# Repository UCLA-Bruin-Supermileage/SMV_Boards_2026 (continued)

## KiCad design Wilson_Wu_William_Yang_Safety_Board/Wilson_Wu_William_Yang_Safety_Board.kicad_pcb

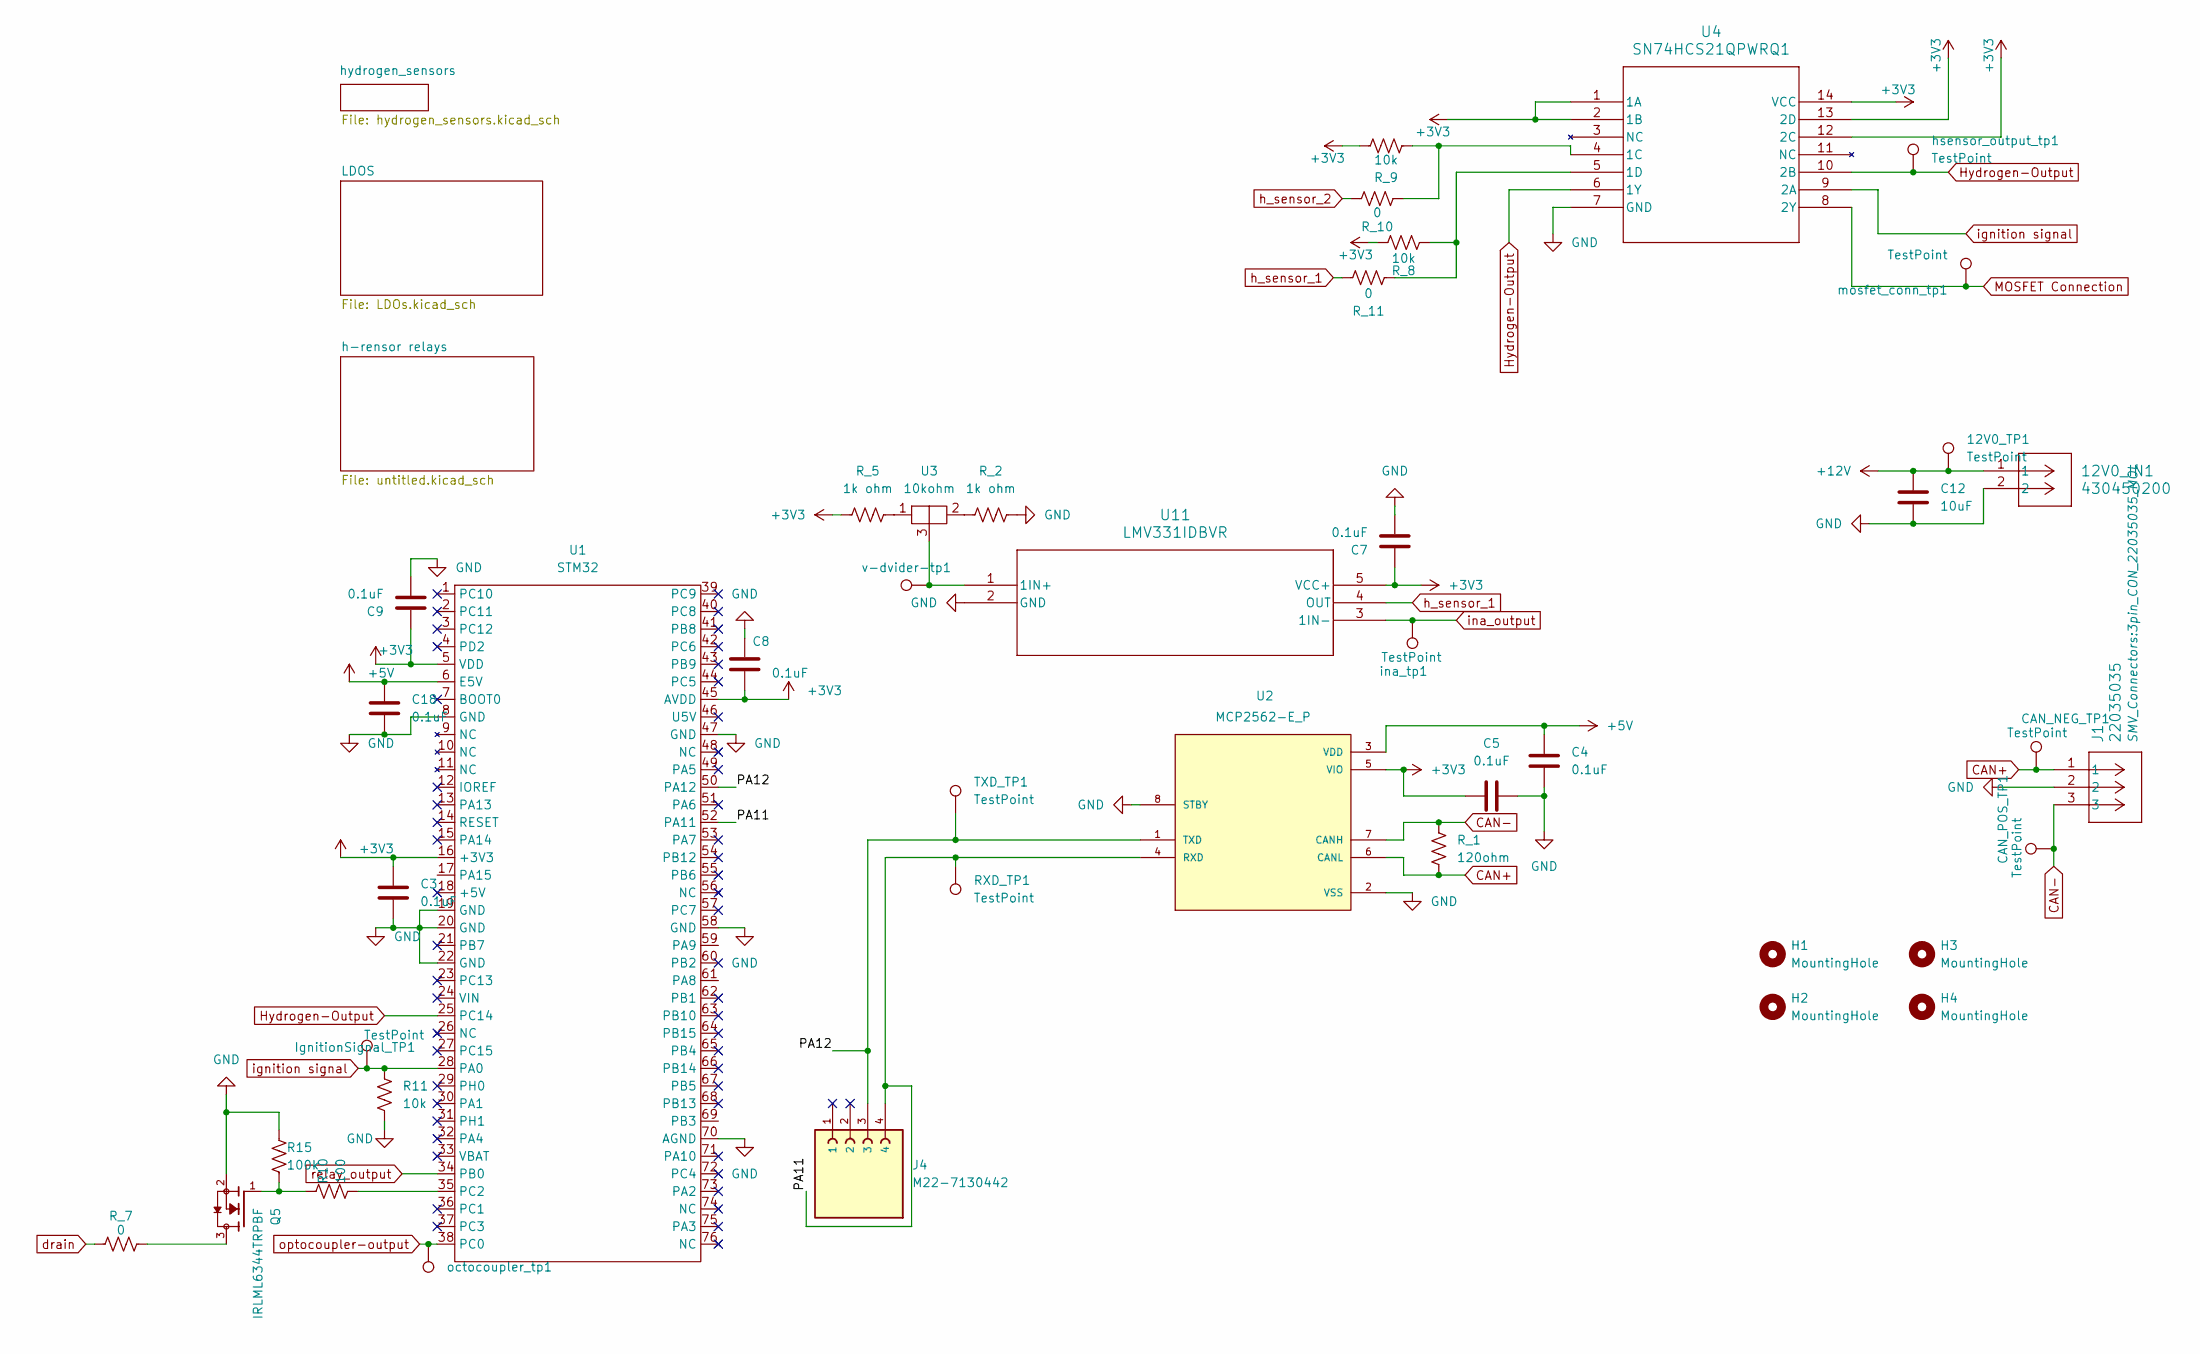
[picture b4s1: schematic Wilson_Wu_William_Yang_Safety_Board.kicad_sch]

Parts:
12V0_IN1: 430450200; CONN_SD-43045-001_02_MOL
12V0_TP1: TestPoint; TestPoint_Pad_D1.0mm
C3, C4, C5, C7, C8, C9, C18: 0.1uF; C_0805_2012Metric
C12: 10uF; C_0805_2012Metric
CAN_NEG_TP1: TestPoint; TestPoint_Pad_D1.0mm
CAN_POS_TP1: TestPoint; TestPoint_Pad_D1.0mm
H1, H2, H3, H4: MountingHole; MountingHole_3.2mm_M3
IgnitionSignal_TP1: TestPoint; TestPoint_Pad_D1.0mm
J1: 22035035; 3pin_CON_22035035_MOL
J4: M22-7130442; HARWIN_M22-7130442
Q5: IRLML6344TRPBF; TRANS_IRLML6344TRPBF; PARTREV December 19, 2014
R10: 100; R_0805_2012Metric
R11: 10k; R_0805_2012Metric
R15: 100k; R_0805_2012Metric
RXD_TP1: TestPoint; TestPoint_Pad_D1.0mm
R_1: 120ohm; R_0805_2012Metric
R_2, R_5: 1k ohm; R_0805_2012Metric
R_7, R_10, R_11: 0; R_0805_2012Metric
R_8, R_9: 10k; R_0805_2012Metric
TXD_TP1: TestPoint; TestPoint_Pad_D1.0mm
U1: STM32; MODULE_NUCLEO-F446RE
U2: MCP2562-E_P; SOIC127P600X175-8N; PARTREV C
U3: 10kohm; Potentiometer_Vishay_T73XW_Horizontal
U4: SN74HCS21QPWRQ1; TSSOP14_PW_TEX-M
U11: LMV331IDBVR; DBV5
hsensor_output_tp1: TestPoint; TestPoint_Pad_D1.0mm
ina_tp1: TestPoint; TestPoint_Pad_D1.0mm
mosfet_conn_tp1: TestPoint; TestPoint_Pad_D1.0mm
octocoupler_tp1: V_DIVIDED; TestPoint_Pad_D1.0mm
v-dvider-tp1: v-dvider-tp; TestPoint_Pad_D1.0mm

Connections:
+3V3: C3.1, C5.2, C7.2, C8.2, C9.2, R_5.1, R_8.2, R_9.2, U1.5 (VDD), U1.16 (+3V3), U1.45 (AVDD), U2.5 (VIO), U4.1 (1A), U4.2 (1B), U4.12 (2C), U4.13 (2D), U4.14 (VCC), U11.5 (VCC+); also elsewhere on the board
+5V: C4.2, C18.2, U1.6 (E5V), U2.3 (VDD); also elsewhere on the board
+12V: 12V0_IN1.1, 12V0_TP1.1, C12.2; also elsewhere on the board
/PA11: J4.4, RXD_TP1.1, U1.52 (PA11), U2.4 (RXD)
/PA12: J4.3, TXD_TP1.1, U1.50 (PA12), U2.1 (TXD)
CAN+: CAN_NEG_TP1.1, J1.1, R_1.2, U2.6 (CANL)
CAN-: CAN_POS_TP1.1, J1.3, R_1.1, U2.7 (CANH)
GND: 12V0_IN1.2, C3.2, C4.1, C5.1, C7.1, C8.1, C9.1, C12.1, C18.1, J1.2, Q5.2, R11.1, R15.2, R_2.2, U1.8 (GND), U1.19 (GND), U1.20 (GND), U1.22 (GND), U1.47 (GND), U1.58 (GND), U1.70 (AGND), U2.2 (VSS), U2.8 (STBY), U4.7 (GND), U11.2 (GND); also elsewhere on the board
Hydrogen-Output: U1.25 (PC14), U4.6 (1Y), U4.10 (2B), hsensor_output_tp1.1
MOSFET Connection: U4.8 (2Y), mosfet_conn_tp1.1; also elsewhere on the board
unnamed: Q5.1, R10.2, R15.1
unnamed: Q5.3, R_7.2
unnamed: R_2.1, U3.2
unnamed: R_5.2, U3.1
unnamed: R10.1, U1.35 (PC2)
unnamed: R_9.1, R_10.1, U4.4 (1C)
unnamed: R_8.1, R_11.1, U4.5 (1D)
unnamed: U3.3, U11.1 (1IN+), v-dvider-tp1.1
drain: R_7.1; also elsewhere on the board
h_sensor_1: R_11.2, U11.4 (OUT)
h_sensor_2: R_10.2; also elsewhere on the board
ignition signal: IgnitionSignal_TP1.1, R11.2, U1.28 (PA0), U4.9 (2A)
ina_output: U11.3 (1IN-), ina_tp1.1; also elsewhere on the board
optocoupler-output: U1.38 (PC0), octocoupler_tp1.1; also elsewhere on the board
relay_output: U1.34 (PB0); also elsewhere on the board

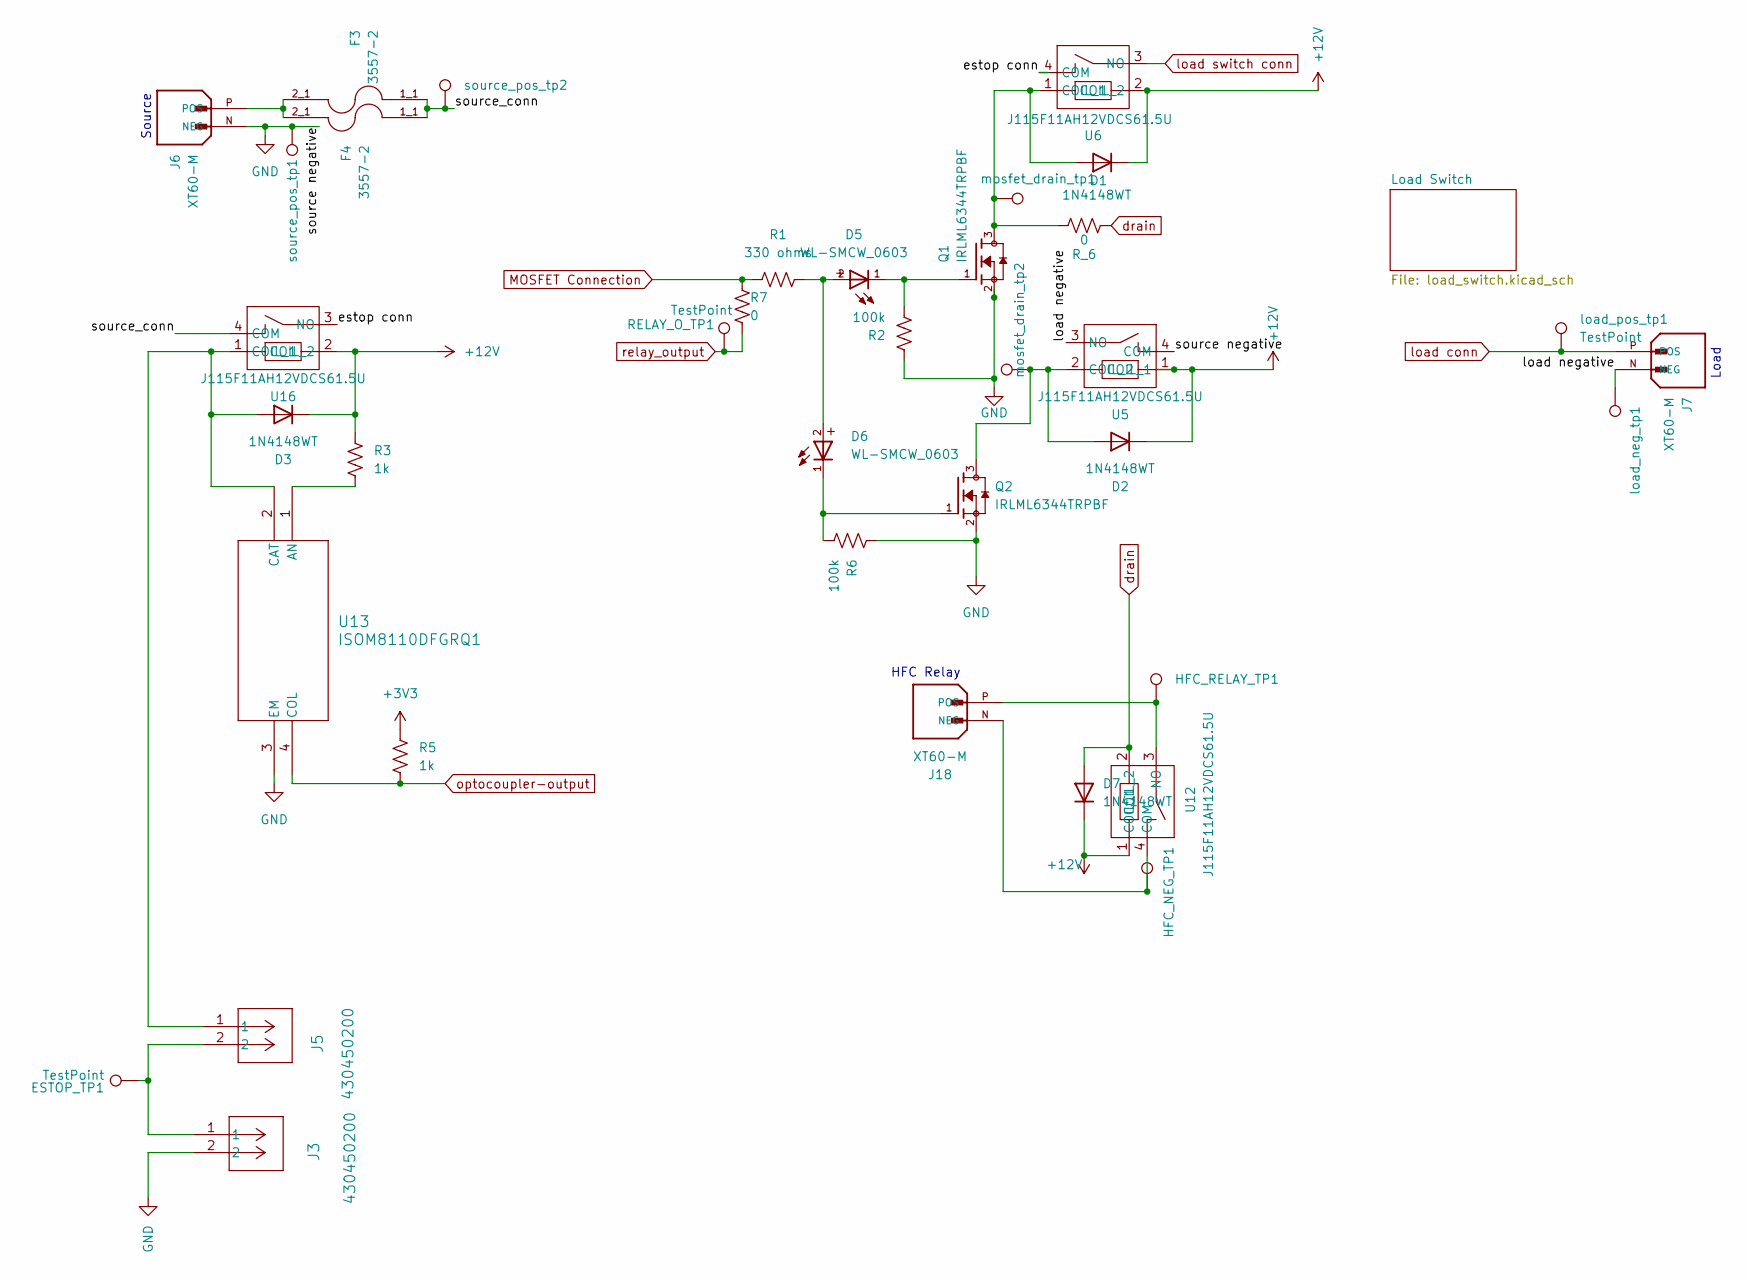
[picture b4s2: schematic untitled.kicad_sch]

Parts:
D1, D2, D3, D7: 1N4148WT; D_SOD-523
D5, D6: WL-SMCW_0603; WL-SMCW_0603(diode)
ESTOP_TP1: TestPoint; TestPoint_Pad_D1.0mm
F3, F4: 3557-2; FUSE_3557-2; PARTREV A
HFC_NEG_TP1: V_DIVIDED; TestPoint_Pad_D1.0mm
HFC_RELAY_TP1: V_DIVIDED; TestPoint_Pad_D1.0mm
J3, J5: 430450200; CONN_SD-43045-001_02_MOL
J6, J7, J18: XT60-M; AMASS_XT60-M; PARTREV V1.2
Q1, Q2: IRLML6344TRPBF; TRANS_IRLML6344TRPBF; PARTREV December 19, 2014
R1: 330 ohms; R_0805_2012Metric
R2, R6: 100k; R_0805_2012Metric
R3, R5: 1k; 0603_resistors
R7: 0; R_0805_2012Metric
RELAY_O_TP1: TestPoint; TestPoint_Pad_D1.0mm
R_6: 0; R_0805_2012Metric
U5, U6, U12, U16: J115F11AH12VDCS61.5U; J115F11AH12VDCS615U
U13: ISOM8110DFGRQ1; DFG0004A_TEX
load_neg_tp1: V_DIVIDED; TestPoint_Pad_D1.0mm
load_pos_tp1: TestPoint; TestPoint_Pad_D1.0mm
mosfet_drain_tp1, mosfet_drain_tp2: V_DIVIDED; TestPoint_Pad_D1.0mm
source_pos_tp1, source_pos_tp2: V_DIVIDED; TestPoint_Pad_D1.0mm

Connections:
+3V3: R5.1; also elsewhere on the board
+12V: D1.1 (K), D2.1 (K), D3.1 (K), D7.1 (K), R3.1, U5.1 (COIL_1), U6.2 (COIL_2), U12.1 (COIL_1), U16.2 (COIL_2); also elsewhere on the board
/h-rensor relays/estop conn: U6.4 (COM), U16.3 (NO)
/h-rensor relays/load negative: J7.N (NEG), U5.3 (NO), load_neg_tp1.1
/h-rensor relays/source_conn: F3.1_1, F4.1_1, U16.4 (COM), source_pos_tp2.1
GND: J3.2, J6.N (NEG), Q1.2, Q2.2, R2.2, R6.2, U5.4 (COM), U13.3 (EM), source_pos_tp1.1; also elsewhere on the board
MOSFET Connection: R1.2, R7.2; also elsewhere on the board
unnamed: D1.2 (A), Q1.3, R_6.2, U6.1 (COIL_1), mosfet_drain_tp1.1
unnamed: D2.2 (A), Q2.3, U5.2 (COIL_2), mosfet_drain_tp2.1
unnamed: D3.2 (A), J5.1, U13.2 (CAT), U16.1 (COIL_1)
unnamed: D5.1, Q1.1, R2.1
unnamed: D5.2, D6.2, R1.1
unnamed: D6.1, Q2.1, R6.1
unnamed: ESTOP_TP1.1, J3.1, J5.2
unnamed: F3.2_1, F4.2_1, J6.P (POS)
unnamed: HFC_NEG_TP1.1, J18.N (NEG), U12.4 (COM)
unnamed: HFC_RELAY_TP1.1, J18.P (POS), U12.3 (NO)
unnamed: R3.2, U13.1 (AN)
drain: D7.2 (A), R_6.1, U12.2 (COIL_2); also elsewhere on the board
load conn: J7.P (POS), load_pos_tp1.1; also elsewhere on the board
load switch conn: U6.3 (NO); also elsewhere on the board
optocoupler-output: R5.2, U13.4 (COL); also elsewhere on the board
relay_output: R7.1, RELAY_O_TP1.1; also elsewhere on the board

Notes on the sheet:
Load
Source
HFC Relay

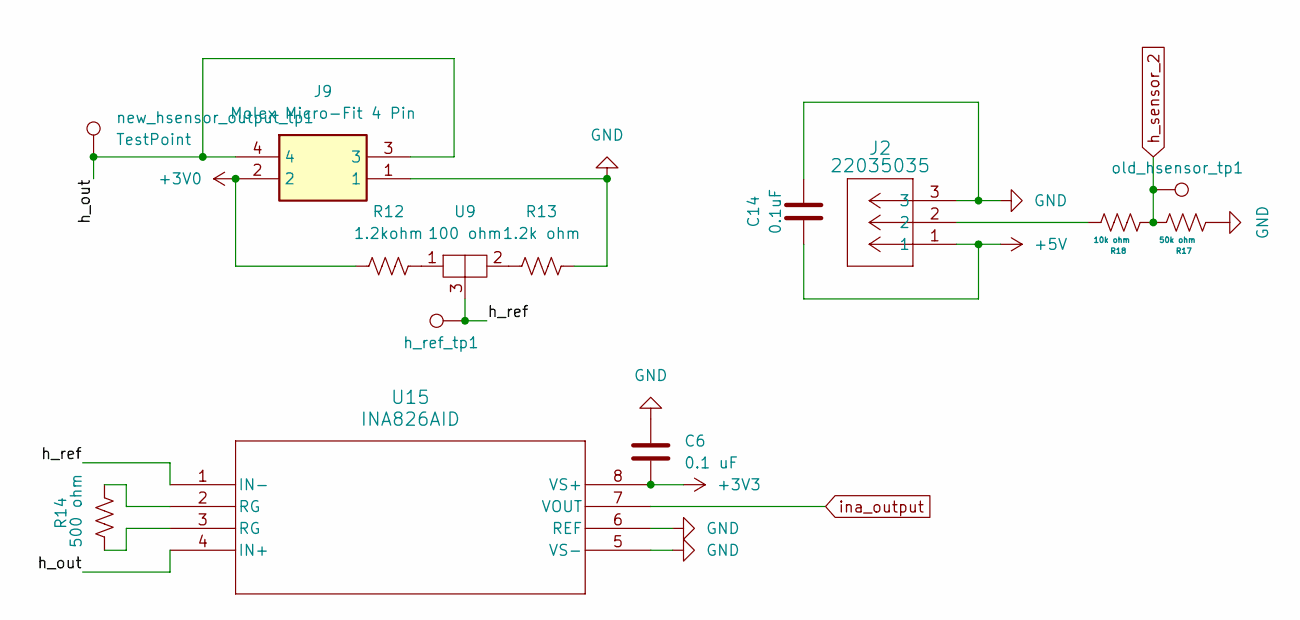
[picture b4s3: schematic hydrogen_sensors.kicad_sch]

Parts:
C6: 0.1 uF; C_0805_2012Metric
C14: 0.1uF; C_0805_2012Metric
J2: 22035035; 3pin_CON_22035035_MOL
J9: Molex Micro-Fit 4 Pin; 4_pin0430450401; Manufacturer_Part_Number 0430450401
R12: 1.2kohm; R_0805_2012Metric
R13: 1.2k ohm; R_0805_2012Metric
R14: 500 ohm; R_0805_2012Metric
R17: 50k ohm; R_0805_2012Metric
R18: 10k ohm; R_0805_2012Metric
U9: 100 ohm; TRIM_PV36W101C01B00
U15: INA826AID; D8-M
h_ref_tp1: TestPoint; TestPoint_Pad_D1.0mm
new_hsensor_output_tp1: TestPoint; TestPoint_Pad_D1.0mm
old_hsensor_tp1: TestPoint; TestPoint_Pad_D1.0mm

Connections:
+3V0: J9.2, R12.1; also elsewhere on the board
+3V3: C6.2, U15.8 (VS+); also elsewhere on the board
+5V: C14.1, J2.1; also elsewhere on the board
/hydrogen_sensors/h_out: J9.3, J9.4, U15.4 (IN+), new_hsensor_output_tp1.1
/hydrogen_sensors/h_ref: U9.3, U15.1 (IN-), h_ref_tp1.1
GND: C6.1, C14.2, J2.3, J9.1, R13.2, R17.1, U15.5 (VS-), U15.6 (REF); also elsewhere on the board
unnamed: J2.2, R18.2
unnamed: R12.2, U9.1
unnamed: R13.1, U9.2
unnamed: R14.1, U15.3 (RG)
unnamed: R14.2, U15.2 (RG)
h_sensor_2: R17.2, R18.1, old_hsensor_tp1.1; also elsewhere on the board
ina_output: U15.7 (VOUT); also elsewhere on the board

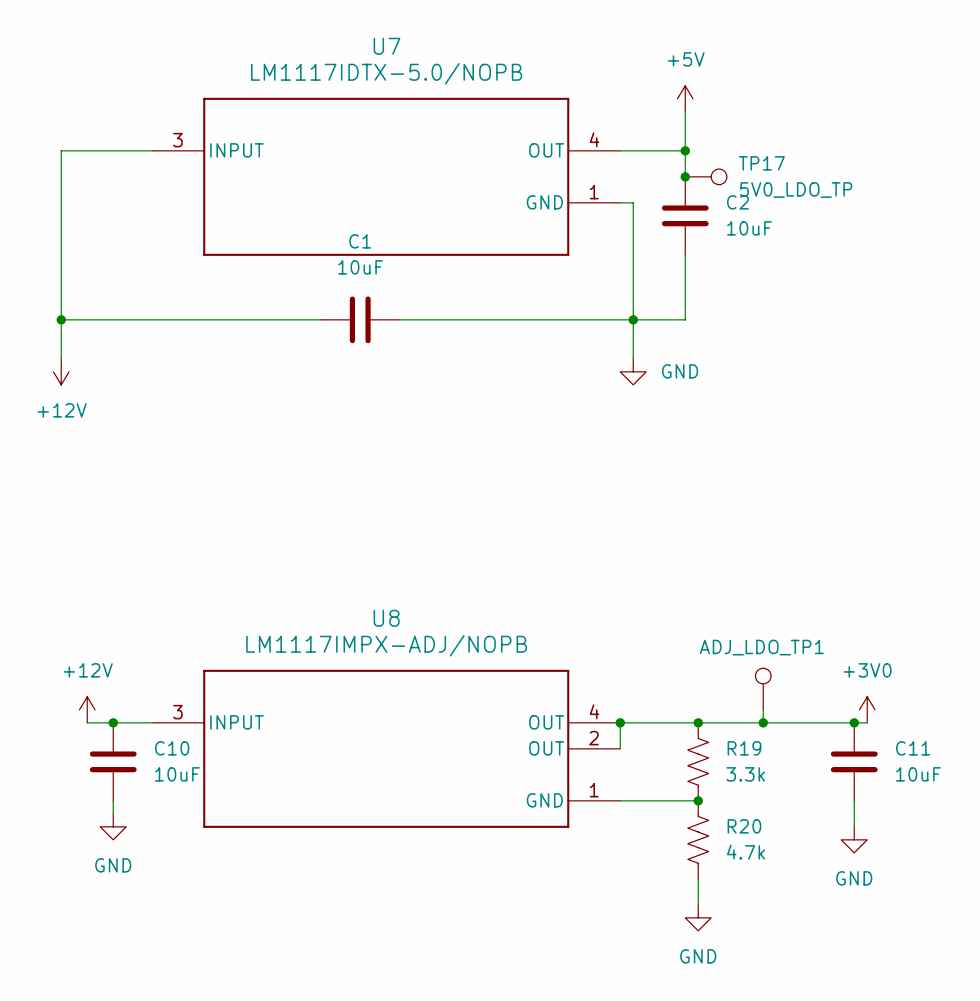
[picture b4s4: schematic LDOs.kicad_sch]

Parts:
ADJ_LDO_TP1: V_DIVIDED; TestPoint_Pad_D1.0mm
C1, C2, C10, C11: 10uF; C_0805_2012Metric
R19: 3.3k; R_0805_2012Metric
R20: 4.7k; R_0805_2012Metric
TP17: 5V0_LDO_TP; TestPoint_Pad_D1.0mm
U7: LM1117IDTX-5.0/NOPB; NDP0003B
U8: LM1117IMPX-ADJ/NOPB; DCY0004A_M

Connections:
+3V0: ADJ_LDO_TP1.1, C11.2, R19.1, U8.2 (OUT), U8.4 (OUT); also elsewhere on the board
+5V: C2.2, TP17.1, U7.4 (OUT); also elsewhere on the board
+12V: C1.1, C10.2, U7.3 (INPUT), U8.3 (INPUT); also elsewhere on the board
GND: C1.2, C2.1, C10.1, C11.1, R20.2, U7.1 (GND); also elsewhere on the board
unnamed: R19.2, R20.1, U8.1 (GND)

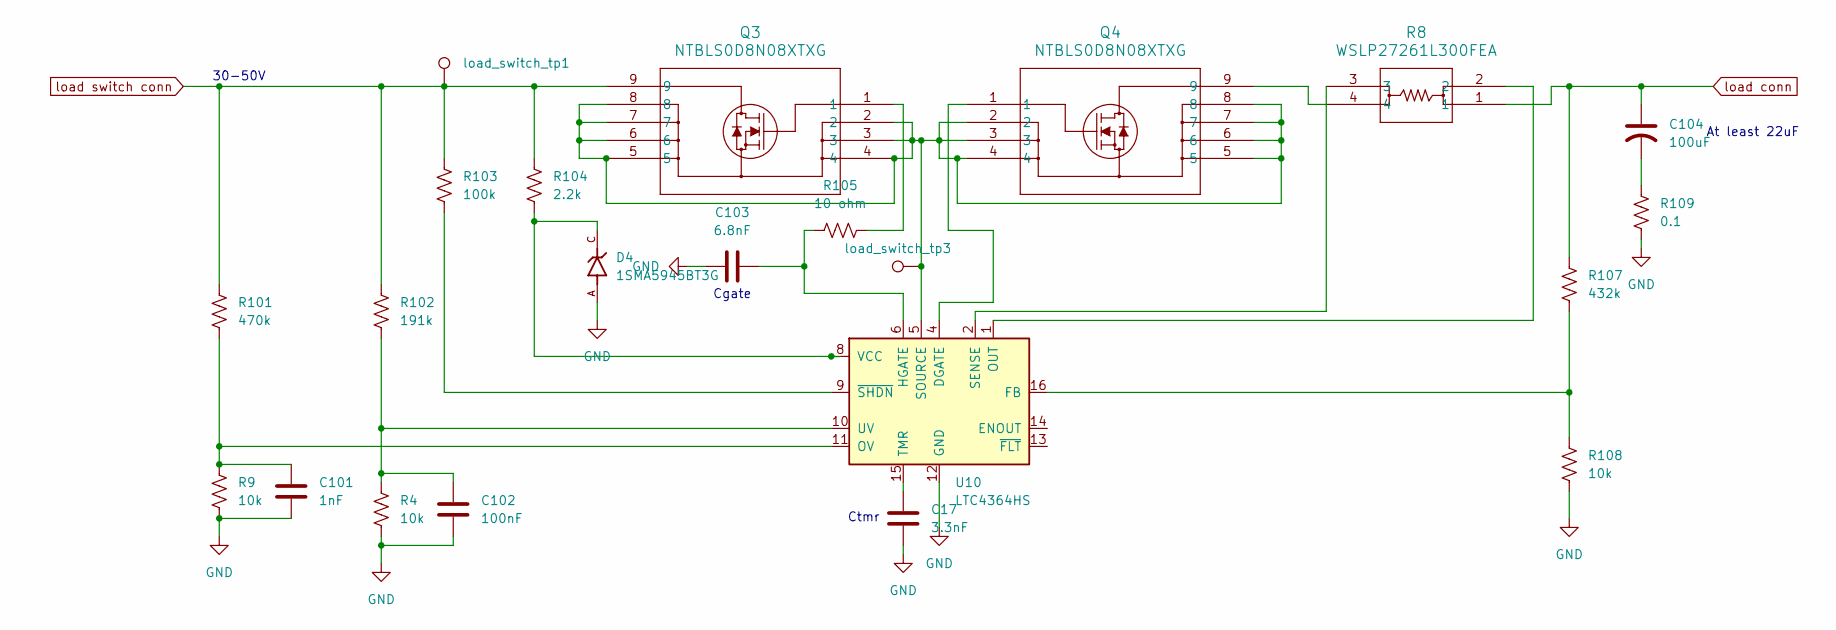
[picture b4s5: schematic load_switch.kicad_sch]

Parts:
C17: 3.3nF; CAPC17595_87N_KEM
C101: 1nF; CAPC17595_87N_KEM
C102: 100nF; CAPC17595_87N_KEM
C103: 6.8nF; CAPC17595_87N_KEM
C104: 100uF; CAPPRD500W60D1000H2200B
D4: 1SMA5945BT3G; DIOM5226X220N; PARTREV 10
Q3, Q4: NTBLS0D8N08XTXG; H-PSOF8L_100CU_ONS_OSI
R4, R9, R108: 10k; 0603_resistors
R8: WSLP27261L300FEA; WSLP2726_1.3mOHM_VIS
R101: 470k; 0603_resistors
R102: 191k; 0603_resistors
R103: 100k; 0603_resistors
R104: 2.2k; 0603_resistors
R105: 10 ohm; 0603_resistors
R107: 432k; 0603_resistors
R109: 0.1; 0603_resistors
U10: LTC4364HS; SOIC-16_3.9x9.9mm_P1.27mm
load_switch_tp1, load_switch_tp3: V_DIVIDED; TestPoint_Pad_D1.0mm

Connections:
GND: C17.2, C101.2, C102.2, C103.1, D4.A, R4.2, R9.2, R108.2, R109.2, U10.12 (GND); also elsewhere on the board
unnamed: C104.2, R109.1
unnamed: Q3.1, R105.2
unnamed: Q4.9, R8.4
unnamed: Q4.1, U10.4 (DGATE)
unnamed: R107.2, R108.1, U10.16 (FB)
unnamed: C103.2, R105.1, U10.6 (HGATE)
unnamed: R8.2, U10.1 (OUT)
unnamed: C101.1, R9.1, R101.2, U10.11 (OV)
unnamed: R8.3, U10.2 (SENSE)
unnamed: Q3.2, Q3.3, Q3.4, Q3.5, Q3.6, Q3.7, Q3.8, Q4.2, Q4.3, Q4.4, Q4.5, Q4.6, Q4.7, Q4.8, U10.5 (SOURCE), load_switch_tp3.1
unnamed: C17.1, U10.15 (TMR)
unnamed: C102.1, R4.1, R102.2, U10.10 (UV)
unnamed: D4.C, R104.2, U10.8 (VCC)
unnamed: R103.2, U10.9 (~SHDN)
load conn: C104.1, R8.1, R107.1; also elsewhere on the board
load switch conn: Q3.9, R101.1, R102.1, R103.1, R104.1, load_switch_tp1.1; also elsewhere on the board

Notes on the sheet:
Cgate
At least 22uF
30-50V
Ctmr

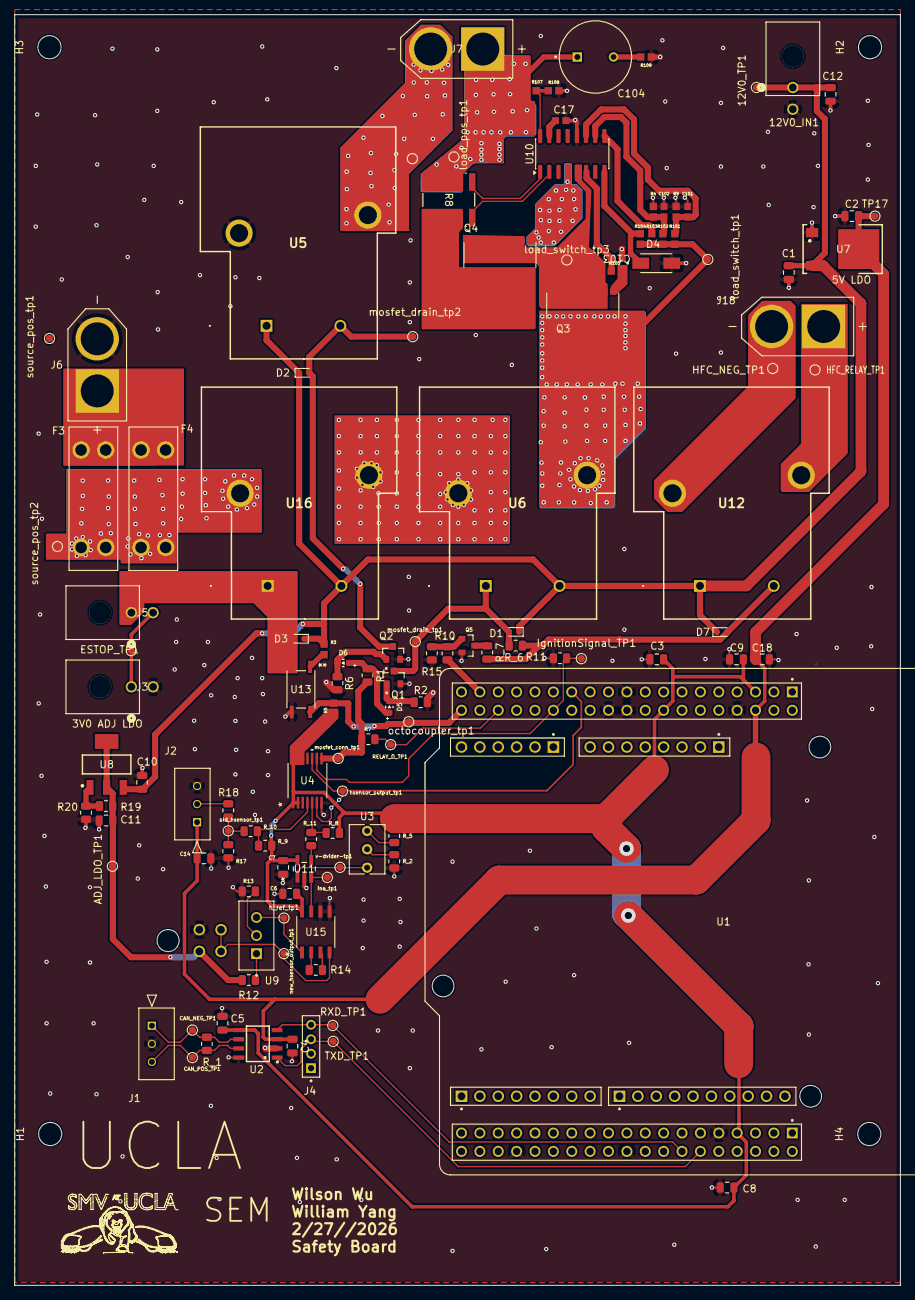
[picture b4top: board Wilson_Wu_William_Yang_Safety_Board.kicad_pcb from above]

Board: 2 copper layers, 122.4 x 175.6 mm, 127 parts (1 on the bottom side), 64 nets.

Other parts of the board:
TP1: TestPoint; SEM_logo

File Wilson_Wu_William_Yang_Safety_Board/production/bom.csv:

Designator,Footprint,Quantity,Value,LCSC Part #
"12V0_IN1, J3, J5",CONN_SD-43045-001_02_MOL,3,430450200,
"12V0_TP1, CAN_NEG_TP1, CAN_POS_TP1, ESTOP_TP1, HSENSOR_OUTPUT_TP1, H_REF_TP1, IGNITIONSIGNAL_TP1, INA_TP1, LOAD_POS_TP1, MOSFET_CONN_TP1, NEW_HSENSOR_OUTPUT_TP1, OLD_HSENSOR_TP1, RELAY_O_TP1, RXD_TP1, TXD_TP1",TestPoint_Pad_D1.0mm,15,TestPoint,
"ADJ_LDO_TP1, HFC_NEG_TP1, HFC_RELAY_TP1, LOAD_NEG_TP1, LOAD_SWITCH_TP1, LOAD_SWITCH_TP3, MOSFET_DRAIN_TP1, MOSFET_DRAIN_TP2, OCTOCOUPLER_TP1, SOURCE_POS_TP1, SOURCE_POS_TP2",TestPoint_Pad_D1.0mm,11,V_DIVIDED,
"C1, C10, C11, C12, C2",0805,5,10uF,
C101,CAPC17595_87N_KEM,1,1nF,
C102,CAPC17595_87N_KEM,1,100nF,
C103,CAPC17595_87N_KEM,1,6.8nF,
C104,CAPPRD500W60D1000H2200B,1,100uF,
"C14, C18, C3, C4, C5, C7, C8, C9",0805,8,0.1uF,
C17,CAPC17595_87N_KEM,1,3.3nF,
C6,0805,1,0.1 uF,
"D1, D2, D3, D7",D_SOD-523,4,1N4148WT,
D4,DIOM5226X220N,1,1SMA5945BT3G,
"D5, D6",WL-SMCW_0603(diode),2,WL-SMCW_0603,
"F3, F4",FUSE_3557-2,2,3557-2,
"J1, J2",3pin_CON_22035035_MOL,2,22035035,
"J18, J6, J7",AMASS_XT60-M,3,XT60-M,
J4,HARWIN_M22-7130442,1,M22-7130442,
J9,4_pin0430450401,1,Molex Micro-Fit 4 Pin,
"Q1, Q2, Q5",TRANS_IRLML6344TRPBF,3,IRLML6344TRPBF,
"Q3, Q4",H-PSOF8L_100CU_ONS_OSI,2,NTBLS0D8N08XTXG,
R1,0805,1,330 ohms,
R10,0805,1,100,
R101,0603_resistors,1,470k,
R102,0603_resistors,1,191k,
R103,0603_resistors,1,100k,
R104,0603_resistors,1,2.2k,
R105,0603_resistors,1,10 ohm,
R107,0603_resistors,1,432k,
"R108, R4, R9",0603_resistors,3,10k,
R109,0603_resistors,1,0.1,
"R11, R_8, R_9",0805,3,10k,
R12,0805,1,1.2kohm,
R13,0805,1,1.2k ohm,
R14,0805,1,500 ohm,
"R15, R2, R6",0805,3,100k,
R17,0805,1,50k ohm,
R18,0805,1,10k ohm,
R19,0805,1,3.3k,
R20,0805,1,4.7k,
"R3, R5",0603_resistors,2,1k,
"R7, R_10, R_11, R_6, R_7",0805,5,0,
R8,WSLP2726_1.3mOHM_VIS,1,WSLP27261L300FEA,
R_1,0805,1,120ohm,
"R_2, R_5",0805,2,1k ohm,
TP1,SEM_logo,1,TestPoint,
TP17,TestPoint_Pad_D1.0mm,1,5V0_LDO_TP,
U1,MODULE_NUCLEO-F446RE,1,STM32,
U10,SOIC-16_3.9x9.9mm_P1.27mm,1,LTC4364HS,
U11,DBV5,1,LMV331IDBVR,
"U12, U16, U5, U6",J115F11AH12VDCS615U,4,J115F11AH12VDCS61.5U,
U13,DFG0004A_TEX,1,ISOM8110DFGRQ1,
U15,D8-M,1,INA826AID,
U2,SOIC127P600X175-8N,1,MCP2562-E_P,
U3,Potentiometer_Vishay_T73XW_Horizontal,1,10kohm,
U4,TSSOP14_PW_TEX-M,1,SN74HCS21QPWRQ1,
U7,NDP0003B,1,LM1117IDTX-5.0/NOPB,
U8,DCY0004A_M,1,LM1117IMPX-ADJ/NOPB,
U9,TRIM_PV36W101C01B00,1,100 ohm,
V-DVIDER-TP1,TestPoint_Pad_D1.0mm,1,v-dvider-tp,

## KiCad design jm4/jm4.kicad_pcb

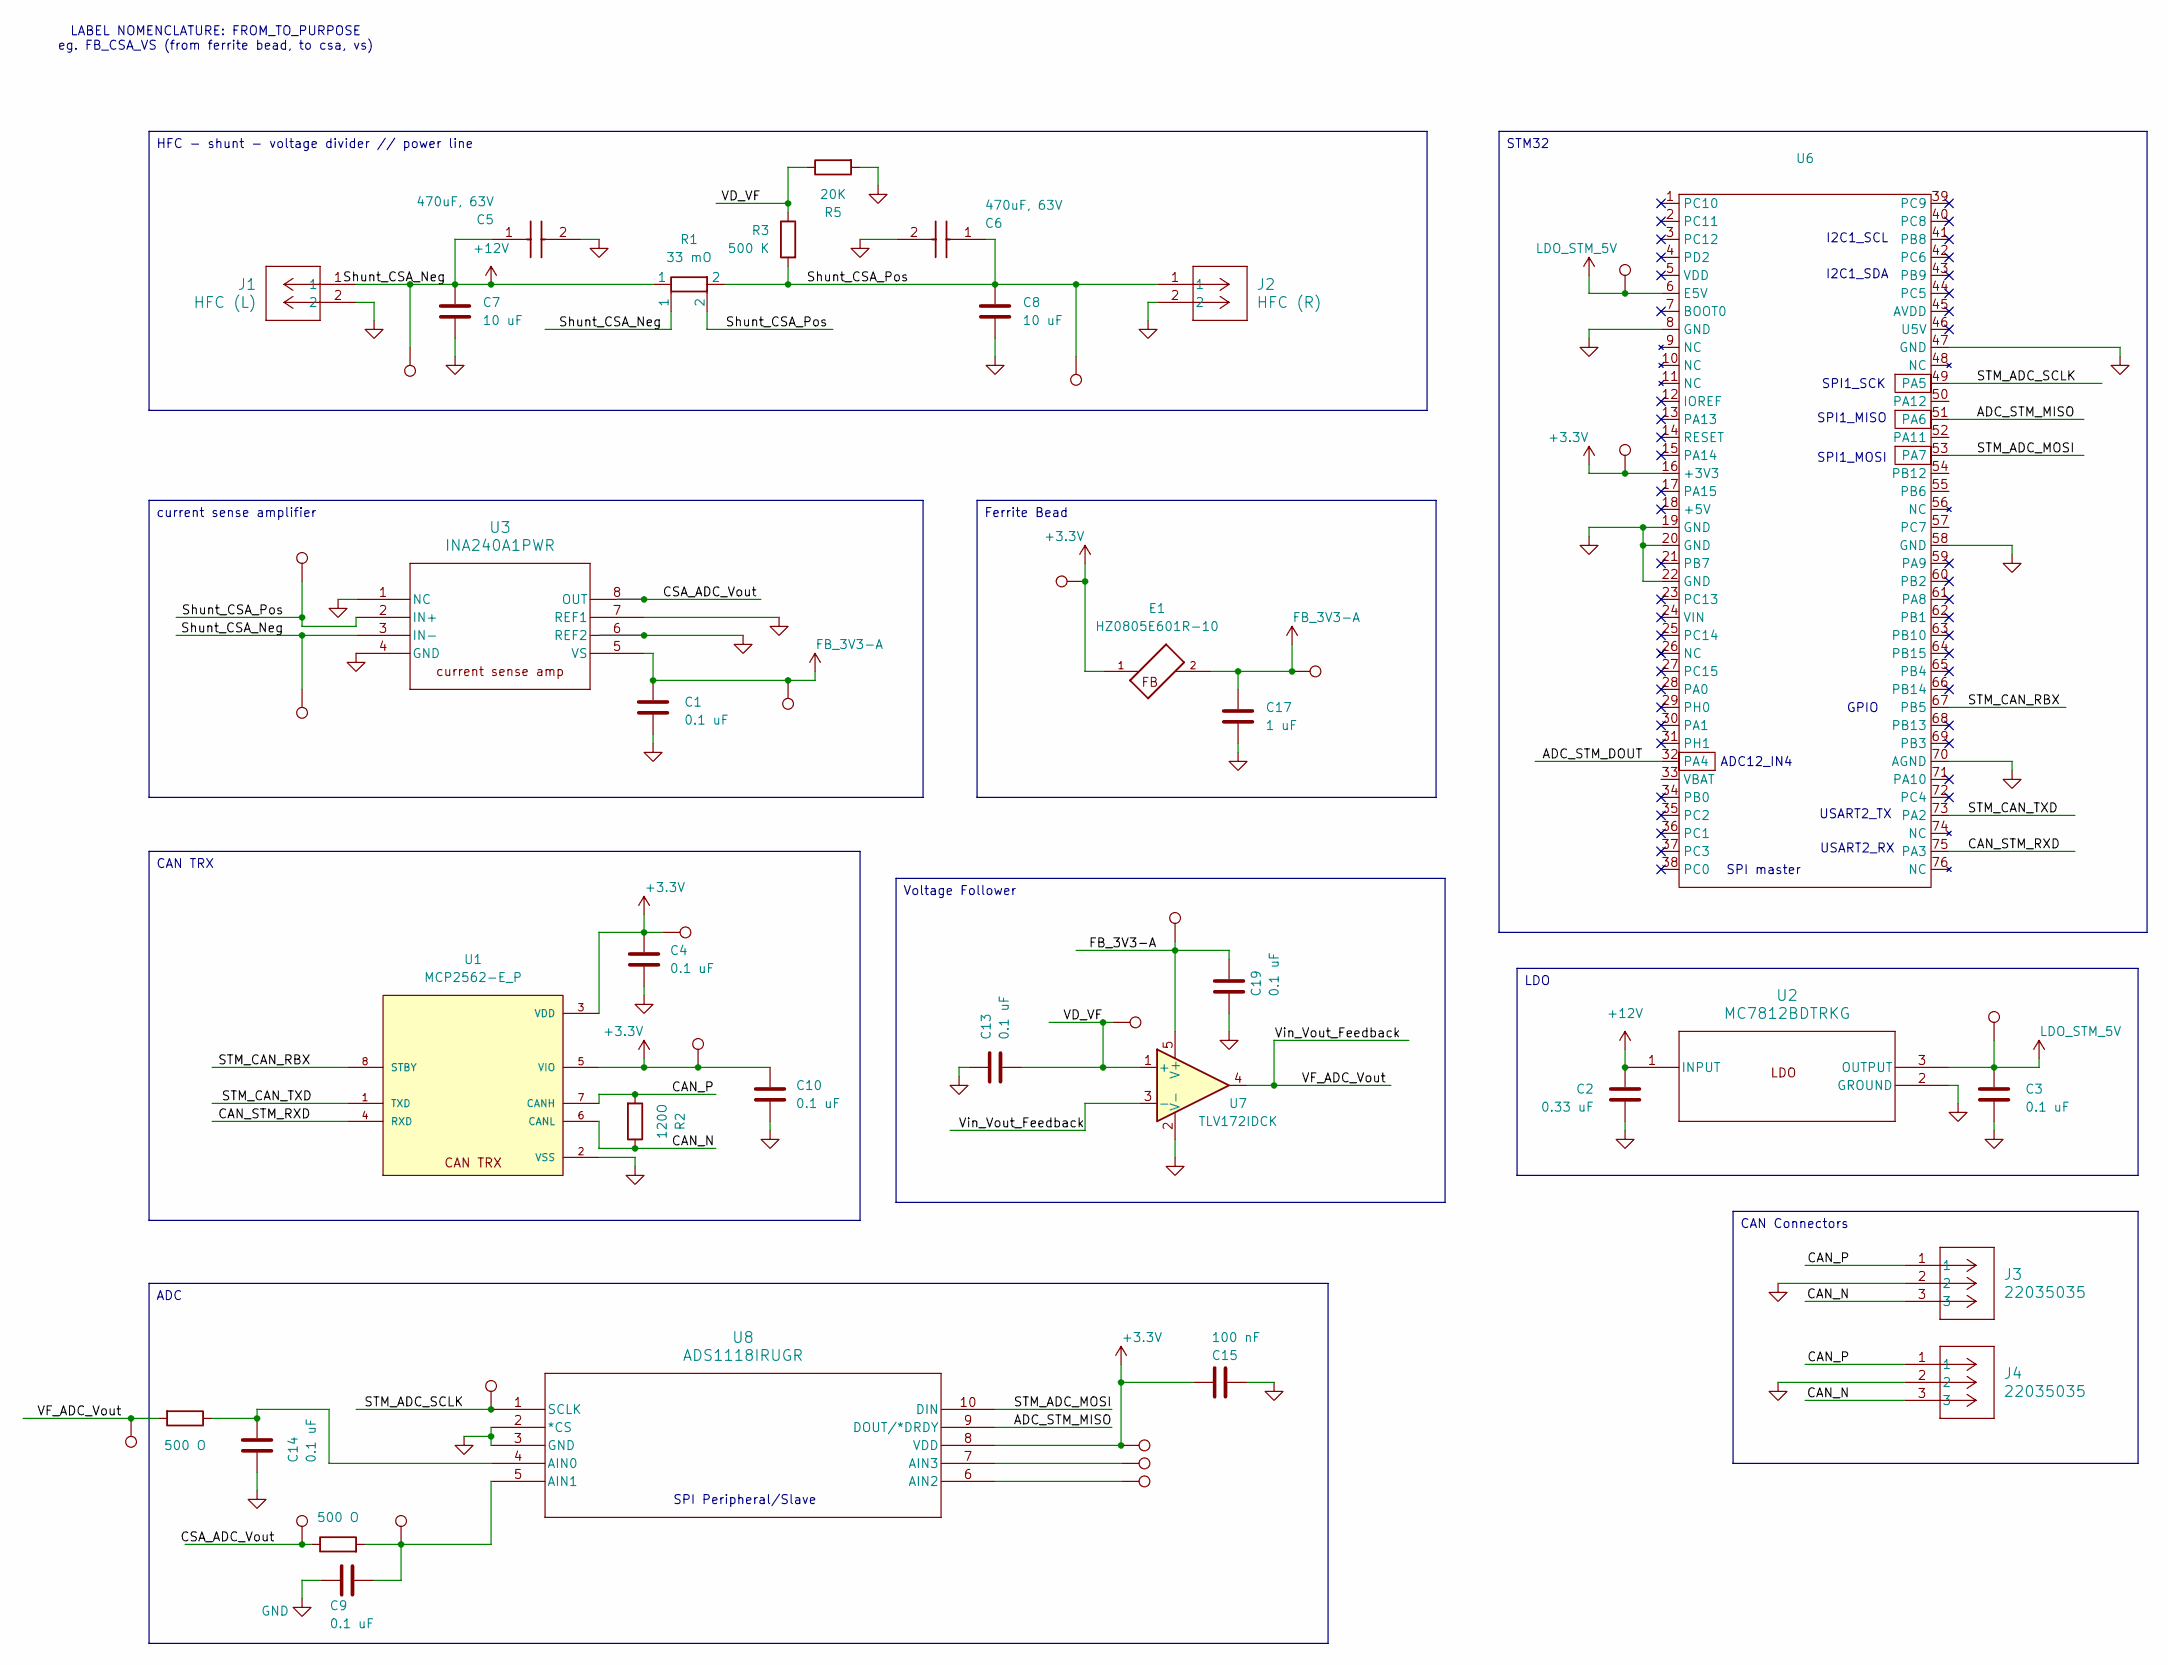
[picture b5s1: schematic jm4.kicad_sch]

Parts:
C1, C3, C4, C9, C10, C13, C14, C19: 0.1 uF; C_0805_2012Metric_Pad1.18x1.45mm_HandSolder
C2: 0.33 uF; C_0805_2012Metric_Pad1.18x1.45mm_HandSolder
C5, C6: 470uF, 63V; Big_Chunky_Cap; Manufacturer_Part_Number C0805C102K5GACTU; Mouser Part Number 80-C0805C102K5G
C7, C8: 10 uF; C_0805_2012Metric_Pad1.18x1.45mm_HandSolder
C15: 100 nF; C_0805_2012Metric_Pad1.18x1.45mm_HandSolder
C17: 1 uF; C_0805_2012Metric_Pad1.18x1.45mm_HandSolder
E1: HZ0805E601R-10; FB_HZ0805E601R-10
J1: HFC (L); CONN_SD-43045-001_02_MOL
J2: HFC (R); CONN_SD-43045-001_02_MOL
J3, J4: 22035035; 3pin_CON_22035035_MOL
R1: 33 mO; RES_PU3921_.5mOHM_YAG
R2: 120O; R_0805_2012Metric_Pad1.20x1.40mm_HandSolder
R3: 500 K; R_0805_2012Metric_Pad1.20x1.40mm_HandSolder
R4, R6: 500 O; R_0805_2012Metric_Pad1.20x1.40mm_HandSolder
R5: 20K; R_0805_2012Metric_Pad1.20x1.40mm_HandSolder
TP1, TP2, TP3, TP4, TP5, TP6, TP7, TP8, TP9, TP10, TP11, TP12, TP13, TP14, TP15, TP16, TP17, TP19, TP20, TP21, TP22: TestPoint; TestPoint_Pad_1.0x1.0mm
U1: MCP2562-E_P; SOIC127P600X175-8N; PARTREV C
U2: MC7812BDTRKG; DPAK-3_ONS
U3: INA240A1PWR; PW0008A_N_TEX
U6: MODULE_NUCLEO-F446RE
U7: TLV172IDCK; SOT-23-5_MC_MCH
U8: ADS1118IRUGR; RUG10 (ADS1118)

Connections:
+3.3V: C4.1, C10.1, C15.2, E1.1, TP12.1, TP13.1, TP15.1, TP17.1, TP22.1, U1.3 (VDD), U1.5 (VIO), U6.16 (+3V3), U8.8 (VDD)
+12V: C2.1, C5.1, C7.1, J1.1, R1.1, TP5.1, TP7.1, U2.1 (INPUT), U3.3 (IN-)
/ADC_STM_DOUT: U6.32 (PA4)
/ADC_STM_MISO: U6.51 (PA6), U8.9 (DOUT/*DRDY)
/CAN_N: J3.3, J4.3, R2.1, U1.6 (CANL)
/CAN_P: J3.1, J4.1, R2.2, U1.7 (CANH)
/CAN_STM_RXD: U1.4 (RXD), U6.75 (PA3)
/CSA_ADC_Vout: R4.1, TP6.1, U3.8 (OUT)
/STM_ADC_MOSI: U6.53 (PA7), U8.10 (DIN)
/STM_ADC_SCLK: TP11.1, U6.49 (PA5), U8.1 (SCLK)
/STM_CAN_RBX: U1.8 (STBY), U6.67 (PB5)
/STM_CAN_TXD: U1.1 (TXD), U6.73 (PA2)
/Shunt_CSA_Pos: C6.1, C8.1, J2.1, R1.2, R3.2, TP4.1, TP8.1, U3.2 (IN+)
/VD_VF: C13.2, R3.1, R5.1, TP16.1, U7.1 (+)
/VF_ADC_Vout: R6.2, TP10.1, U7.3 (-), U7.4
FB_3V3-A: C1.1, C17.1, C19.2, E1.2, TP14.1, TP19.1, TP20.1, U3.5 (VS), U7.5 (V+)
GND: C1.2, C2.2, C3.2, C4.2, C5.2, C6.2, C7.2, C8.2, C9.2, C10.2, C13.1, C14.2, C15.1, C17.2, C19.1, J1.2, J2.2, J3.2, J4.2, R5.2, U1.2 (VSS), U2.2 (GROUND), U3.1 (NC), U3.4 (GND), U3.6 (REF2), U3.7 (REF1), U6.8 (GND), U6.19 (GND), U6.20 (GND), U6.22 (GND), U6.47 (GND), U6.58 (GND), U6.70 (AGND), U7.2 (V-), U8.2 (*CS), U8.3 (GND)
LDO_STM_5V: C3.1, TP3.1, TP21.1, U2.3 (OUTPUT), U6.6 (E5V)
unnamed: C14.1, R6.1, U8.4 (AIN0)
unnamed: C9.1, R4.2, TP9.1, U8.5 (AIN1)
unnamed: TP1.1, U8.6 (AIN2)
unnamed: TP2.1, U8.7 (AIN3)

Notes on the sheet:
USART2_TX
GPIO
USART2_RX
SPI1_MOSI
SPI1_MISO
I2C1_SCL
I2C1_SDA
ADC12_IN4
SPI Peripheral/Slave
SPI1_SCK
LABEL NOMENCLATURE: FROM_TO_PURPOSE eg. FB_CSA_VS (from ferrite bead, to csa, vs)
SPI master
STM32
current sense amplifier
ADC
LDO
Voltage Follower
CAN TRX
HFC - shunt - voltage divider // power line
CAN Connectors
Ferrite Bead

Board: 4 copper layers, 53 parts (0 on the bottom side), 21 nets, no tracks yet.
